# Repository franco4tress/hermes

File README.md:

NUCLEO-H753ZI + TB6612FNG — Quick Start

Summary
- Minimal firmware to drive one TB6612FNG channel from a NUCLEO-H753ZI.
- Uses `stm32h7xx-hal` and `embedded-hal` (0.2) — built for `thumbv7em-none-eabihf`.

Pin mapping (current firmware)
- PWMA (PWM speed):     PB9 (CN7)
- AIN1 (direction):     PB15 (CN7)
- AIN2 (direction):     PA15 (CN7)
- STBY (enable):        PB12 (CN7)
- TB6612 VCC:           NUCLEO 3.3 V
- TB6612 GND:           NUCLEO GND and Battery negative (common ground)
- TB6612 VM:            Battery +12 V (motor supply)

Wiring notes
- Connect TB6612 GND to BOTH the NUCLEO GND and the battery negative (B−). This common ground is required for logic signals to be referenced correctly.
- VCC on TB6612 must be 3.3 V from the NUCLEO (not battery +12 V).
- STBY must be pulled HIGH (firmware drives `PB12` high) to enable outputs.
- Use the Morpho `CN7` cluster (PB9/PB15/PA15/PB12) for compact wiring as shown above.

Build & flash
- Ensure target and runner are set in `.cargo/config.toml` (probe-rs runner configured).
- Build and flash in one step (requires probe-rs and a connected ST-LINK):

```bash
cargo run --release
```

Troubleshooting checklist
1. Power off. Verify wiring matches the pin mapping above.
2. Confirm TB6612 VCC = 3.3 V and VM = battery +12 V.
3. Confirm continuity: NUCLEO GND ⇄ TB6612 GND ⇄ Battery negative.
4. Run firmware; verify STBY pin reads ~3.3 V when firmware starts.
5. Probe PWM pin (PB9) with logic probe / scope — should see PWM bursts during the demo.
6. If logic signals are present but motor doesn't spin, verify VM and motor connections (A01/A02) and that the motor can draw required current.

If you want, I can add a PNG wiring diagram and a CN7 pin-index reference into the repo.

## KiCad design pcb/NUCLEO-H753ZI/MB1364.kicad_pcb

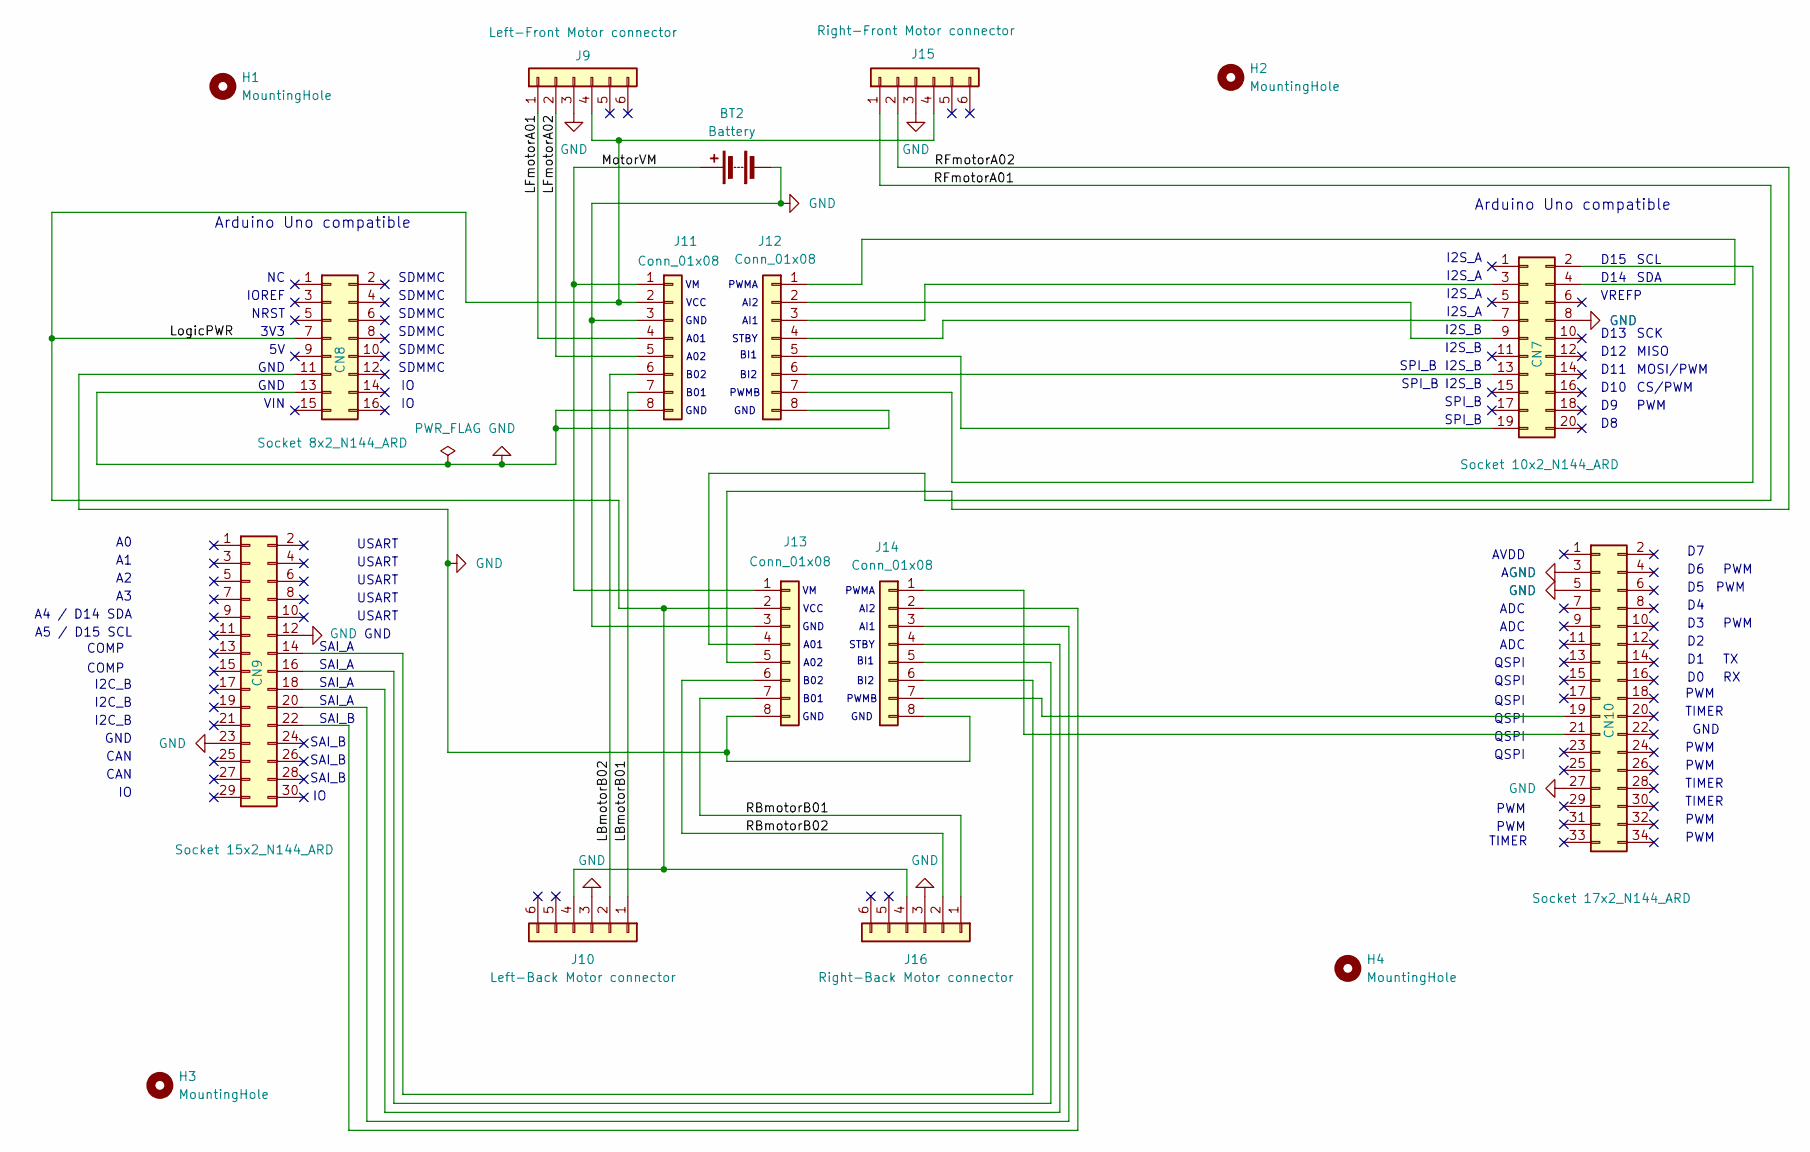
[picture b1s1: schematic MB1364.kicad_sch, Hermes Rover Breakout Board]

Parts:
BT2: Battery; TerminalBlock_Phoenix_MKDS-1,5-2-5.08_1x02_P5.08mm_Horizont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; Manufacturer Part Number 1715721; LCSC C480516
CN7: Socket 10x2_N144_ARD; CON_SAMTEC_SSW-110-23-X-D_N144_ARD; PART_TYPE Connector; LCSC C3323653
CN8: Socket 8x2_N144_ARD; CON_SAMTEC_SSW-108-23-X-D_N144_ARD; PART_TYPE Connector; LCSC C7019038
CN9: Socket 15x2_N144_ARD; CON_SAMTEC_SSW-115-23-X-D_N144_ARD; PART_TYPE Connector; LCSC C5761790
CN10: Socket 17x2_N144_ARD; CON_SAMTEC_SSW-117-23-X-D_N144_ARD; PART_TYPE Connector; LCSC C7322411
H1, H2, H3, H4: MountingHole; MountingHole_3.2mm_M3
J9: Left-Front Motor connector; PinHeader_1x06_P2.00mm_Horizontal; Manufacturer Part Number 2PH1R-06-UA; LCSC C5495614
J10: Left-Back Motor connector; PinHeader_1x06_P2.00mm_Horizontal; Manufacturer Part Number 2PH1R-06-UA; LCSC C5495614
J11, J12, J13, J14: Conn_01x08; PinSocket_1x08_P2.00mm_Vertical; Manufacturer Part Number 2RS1-08-G; LCSC C3319810
J15: Right-Front Motor connector; PinHeader_1x06_P2.00mm_Horizontal; Manufacturer Part Number 2PH1R-06-UA; LCSC C5495614
J16: Right-Back Motor connector; PinHeader_1x06_P2.00mm_Horizontal; Manufacturer Part Number 2PH1R-06-UA; LCSC C5495614

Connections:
/LBmotorB01: J10.1, J11.7
/LBmotorB02: J10.2, J11.6
/LFmotorA01: J9.1, J11.4
/LFmotorA02: J9.2, J11.5
/LogicPWR: CN8.7, J9.4, J10.4, J11.2, J13.2, J15.4, J16.4
/MotorVM: BT2.1 (+), J11.1, J13.1
/RBmotorB01: J13.7, J16.1
/RBmotorB02: J13.6, J16.2
/RFmotorA01: J13.4, J15.1
/RFmotorA02: J13.5, J15.2
GND: BT2.2 (-), CN7.8, CN8.11, CN8.13, CN9.12, CN9.23, CN10.3, CN10.5, CN10.27, J9.3, J10.3, J11.3, J11.8, J12.8, J13.3, J13.8, J14.8, J15.3, J16.3
unnamed: CN7.2, J12.7
unnamed: CN7.3, J12.3
unnamed: CN7.4, J12.1
unnamed: CN7.7, J12.4
unnamed: CN7.9, J12.2
unnamed: CN7.13, J12.6
unnamed: CN7.19, J12.5
unnamed: CN9.14, J14.6
unnamed: CN9.16, J14.5
unnamed: CN9.18, J14.4
unnamed: CN9.20, J14.3
unnamed: CN9.22, J14.2
unnamed: CN10.19, J14.7
unnamed: CN10.21, J14.1

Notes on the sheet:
SPI_B
I2S_A
GND
CAN
MISO
AI1
SAI_B
PWM
B02
SAI_A
MOSI/PWM
SDA
SDMMC
TIMER
AI2
VIN
D13
STBY
I2C_B
COMP
ADC
QSPI
PWMB
CS/PWM
SCK
VCC
USART
A01
A5 / D15 SCL
Arduino Uno compatible
PWMA
D11
A02
D15
NRST
BI1
A4 / D14 SDA
IOREF
AGND
VREFP

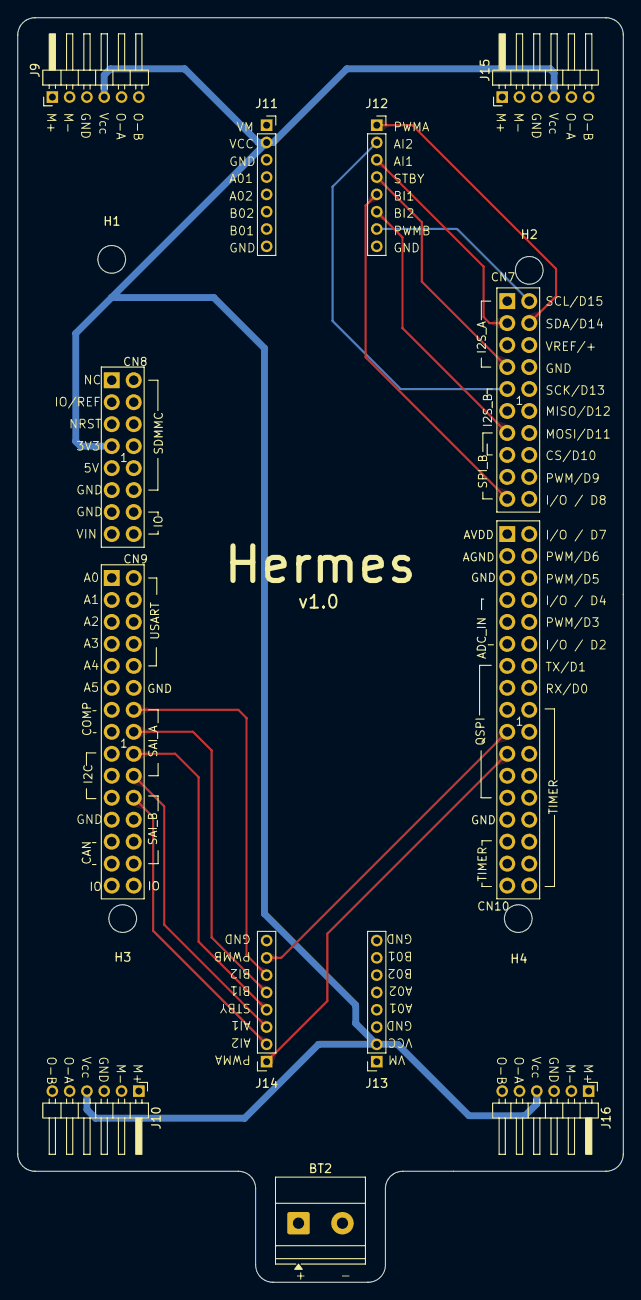
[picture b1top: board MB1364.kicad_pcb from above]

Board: 4 copper layers, 70.0 x 146.2 mm, 17 parts (0 on the bottom side), 25 nets.

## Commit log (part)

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2026-03-13 Initial project setup with STM32H753ZI support, including configuration files, dependencies, and example code for TB6612FNG motor control.
2026-03-13 Fix GPIO pin assignment for AIN2 to avoid conflict with Ethernet PHY
2026-03-13 Update README and main.rs for correct AIN2 pin mapping and motor reverse speed
2026-03-14 Refactor motor control implementation and adjust forward/reverse speed parameters.
2026-04-07 Add configuration for left motor and update PWM channel setup.
2026-04-17 Modified polarization logic to use a new enum.
2026-04-17 Added logic for smooth driving (with temporary blocking delay).
2026-06-25 Enhance motor control by adding left motor operations for forward, reverse, and braking sequences
